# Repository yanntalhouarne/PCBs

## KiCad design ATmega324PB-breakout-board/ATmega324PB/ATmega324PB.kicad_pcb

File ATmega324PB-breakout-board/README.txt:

Breakout board for the ATmega324PB (automative rated)

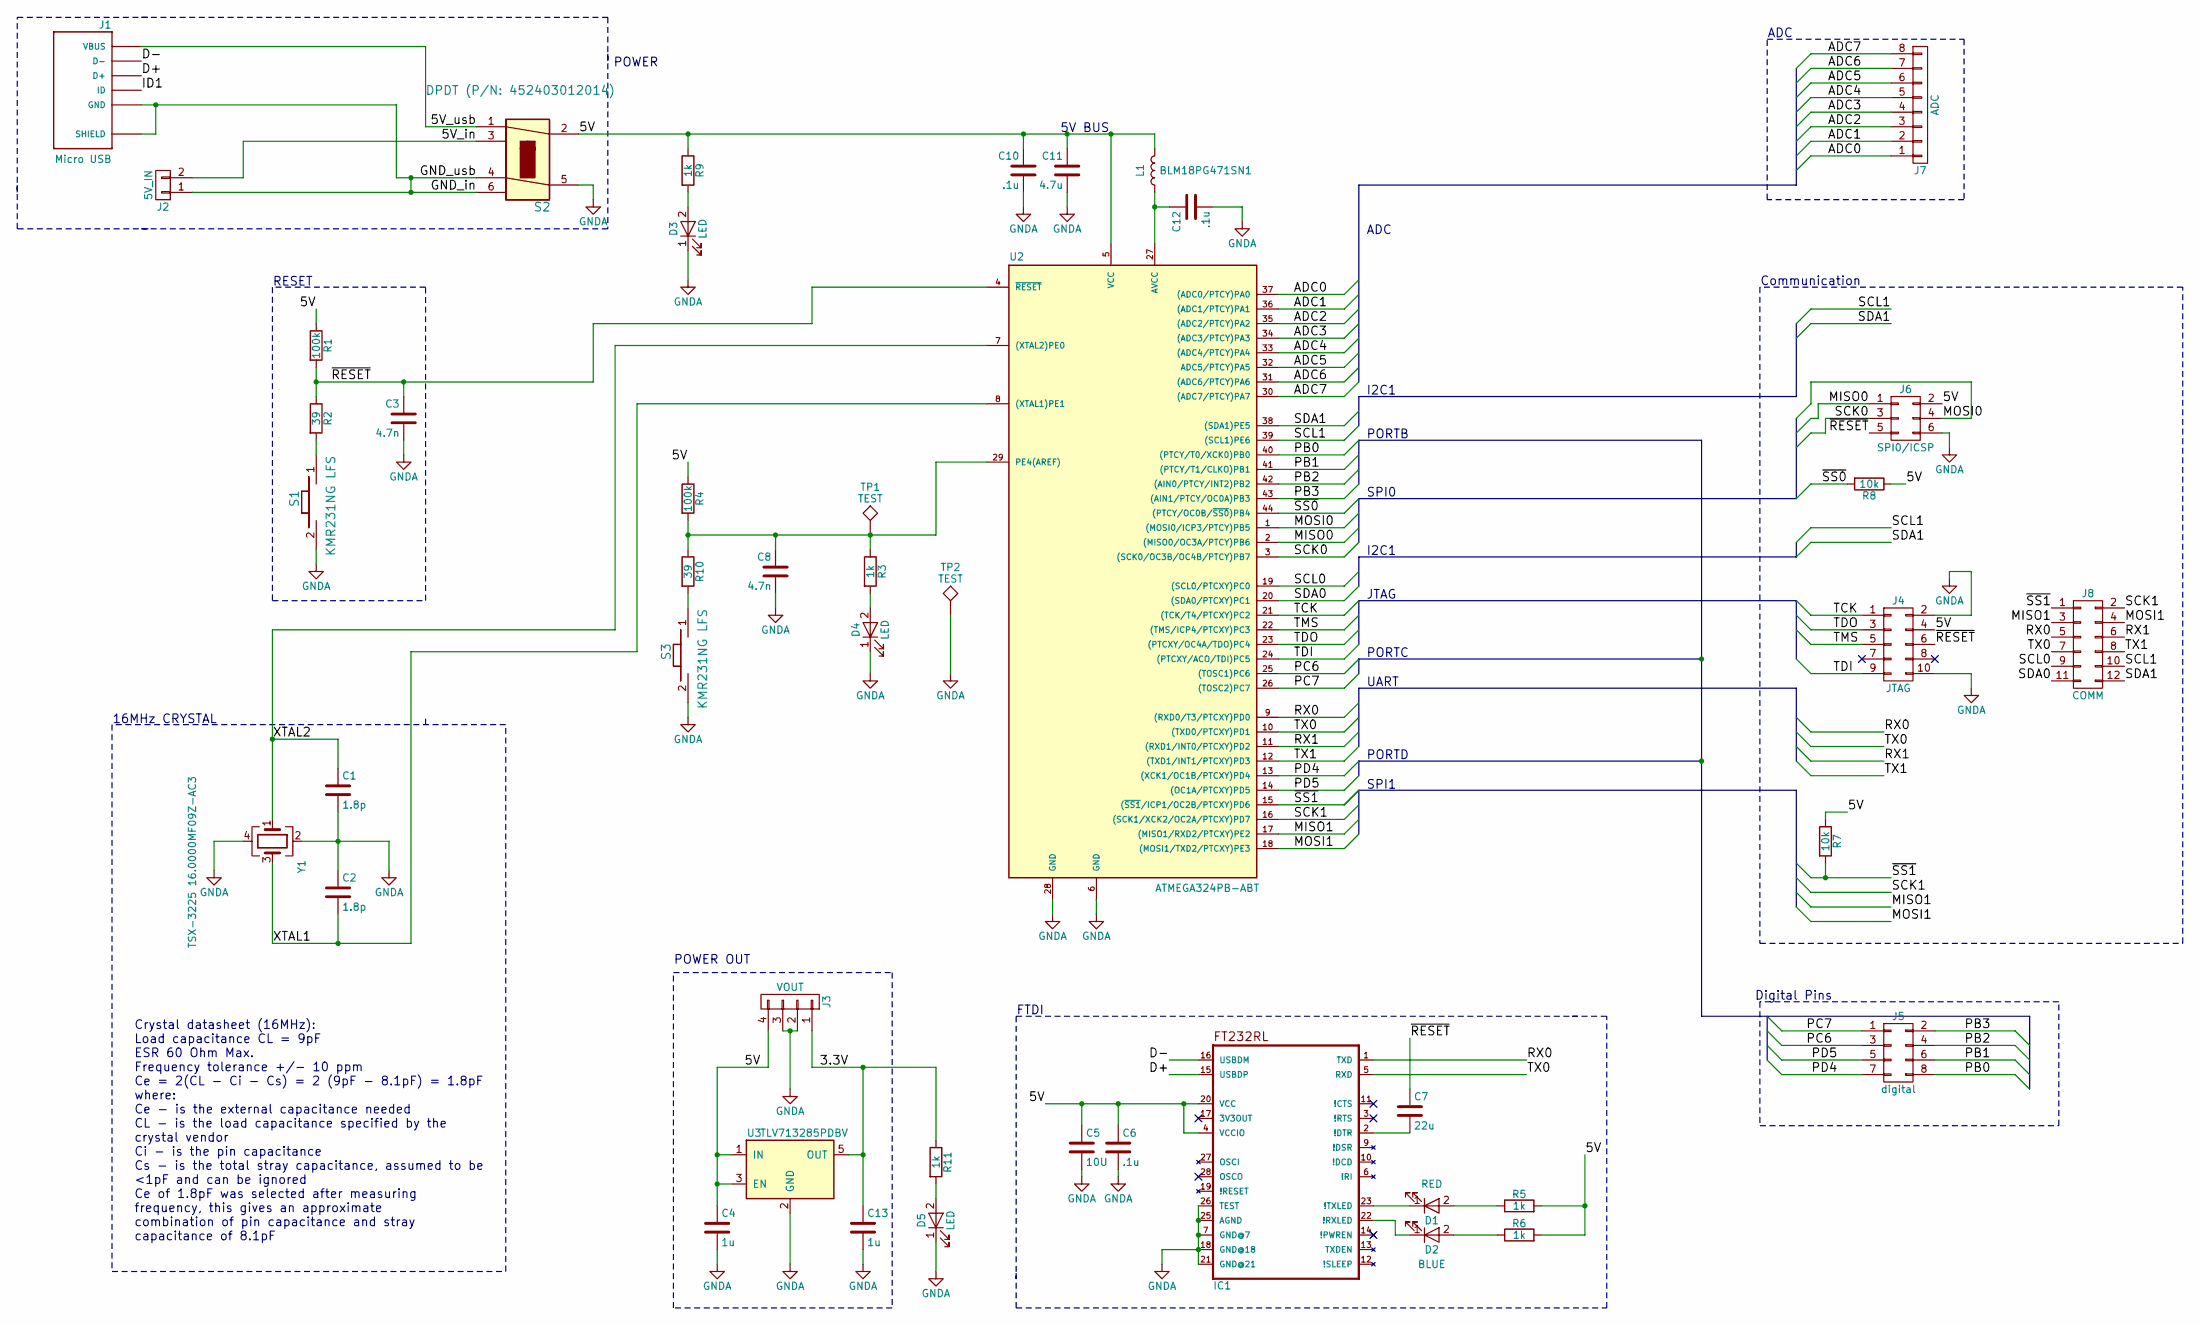
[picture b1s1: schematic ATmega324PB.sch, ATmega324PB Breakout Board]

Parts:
C1, C2: 1.8p; C_0402
C3, C8: 4.7n; C_0402
C4, C13: 1u; C_0402
C5: 10U; C_0603
C6, C10, C12: .1u; C_0402
C7: 22u; C_0603
C11: 4.7u; C_0603
D1: RED; LED_0603
D2: BLUE; LED_0603
D3, D4, D5: LED; LED_0603
IC1: FT232RL; SSOP28-LD
J1: Micro USB; USB_10118192-0001LF
J2: 5V_IN; Pin_Header_Straight_1x02_Pitch2.54mm
J3: VOUT; Pin_Header_Straight_1x04_Pitch2.54mm
J4: JTAG; Pin_Header_Straight_2x05_Pitch1.27mm
J5: digital; Pin_Header_Straight_2x04_Pitch2.54mm
J6: SPI0/ICSP; Pin_Header_Straight_2x03_Pitch2.54mm
J7: ADC; Pin_Header_Straight_1x08_Pitch2.54mm
J8: COMM; Pin_Header_Straight_2x06_Pitch2.54mm
L1: BLM18PG471SN1; L_0603
R1, R4: 100k; R_0402
R2, R10: 39; R_0402
R3: 1k; R_0603
R5, R6, R9, R11: 1k; R_0402
R7, R8: 10k; R_0402
S1, S3: KMR231NG LFS; SW_SPST_KMR2
S2: DPDT (P/N: 452403012014); JS202011SCQN
TP1, TP2: TEST; Pin_Header_Straight_1x01_Pitch1.00mm
U2: ATMEGA324PB-ABT; QFP80P1200X1200X120-44N
U3: TLV713285PDBV; SOT-23-5
Y1: TSX-3225 16.0000MF09Z-AC3; TSX_3225_16MF09ZAC3

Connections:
/3.3V: C13.1, J3.1, R11.1, U3.5 (OUT)
/5V: C4.1, C5.1, C6.1, C10.1, C11.1, IC1.4 (VCCIO), IC1.20 (VCC), J3.4, J4.4, J6.2, L1.2, R1.1, R4.1, R5.2, R6.2, R7.1, R8.1, R9.1, S2.2, U2.5 (VCC), U3.1 (IN), U3.3 (EN)
/5V_in: J2.2, S2.3
/5V_usb: J1.1 (VBUS), S2.1
/ADC0: J7.1, U2.37 ((ADC0/PTCY)PA0)
/ADC1: J7.2, U2.36 ((ADC1/PTCY)PA1)
/ADC2: J7.3, U2.35 ((ADC2/PTCY)PA2)
/ADC3: J7.4, U2.34 ((ADC3/PTCY)PA3)
/ADC4: J7.5, U2.33 ((ADC4/PTCY)PA4)
/ADC5: J7.6, U2.32 (ADC5/PTCY)PA5)
/ADC6: J7.7, U2.31 ((ADC6/PTCY)PA6)
/ADC7: J7.8, U2.30 ((ADC7/PTCY)PA7)
/D+: IC1.15 (USBDP), J1.3 (D+)
/D-: IC1.16 (USBDM), J1.2 (D-)
/GND_in: J1.5 (GND), J1.6 (SHIELD), J1.7 (SHIELD), J1.8 (SHIELD), J1.9 (SHIELD), J2.1, S2.4, S2.6
/MISO0: J6.1, U2.2 ((MISO0/OC3A/PTCY)PB6)
/MISO1: J8.3, U2.17 ((MISO1/RXD2/PTCXY)PE2)
/MOSI0: J6.4, U2.1 ((MOSI0/ICP3/PTCY)PB5)
/MOSI1: J8.4, U2.18 ((MOSI1/TXD2/PTCXY)PE3)
/PB0: J5.8, U2.40 ((PTCY/T0/XCK0)PB0)
/PB1: J5.6, U2.41 ((PTCY/T1/CLKO)PB1)
/PB2: J5.4, U2.42 ((AIN0/PTCY/INT2)PB2)
/PB3: J5.2, U2.43 ((AIN1/PTCY/OC0A)PB3)
/PC6: J5.3, U2.25 ((TOSC1)PC6)
/PC7: J5.1, U2.26 ((TOSC2)PC7)
/PD4: J5.7, U2.13 ((XCK1/OC1B/PTCXY)PD4)
/PD5: J5.5, U2.14 ((OC1A/PTCXY)PD5)
/RX0: IC1.1 (TXD), J8.5, U2.9 ((RXD0/T3/PTCXY)PD0)
/RX1: J8.6, U2.11 ((RXD1/INT0/PTCXY)PD2)
/SCK0: J6.3, U2.3 ((SCK0/OC3B/OC4B/PTCY)PB7)
/SCK1: J8.2, U2.16 ((SCK1/XCK2/OC2A/PTCXY)PD7)
/SCL0: J8.9, U2.19 ((SCL0/PTCXY)PC0)
/SCL1: J8.10, U2.39 ((SCL1)PE6)
/SDA0: J8.11, U2.20 ((SDA0/PTCXY)PC1)
/SDA1: J8.12, U2.38 ((SDA1)PE5)
/TCK: J4.1, U2.21 ((TCK/T4/PTCXY)PC2)
/TDI: J4.9, U2.24 ((PTCXY/ACO/TDI)PC5)
/TDO: J4.3, U2.23 ((PTCXY/OC4A/TDO)PC4)
/TMS: J4.5, U2.22 ((TMS/ICP4/PTCXY)PC3)
/TX0: IC1.5 (RXD), J8.7, U2.10 ((TXD0/PTCXY)PD1)
/TX1: J8.8, U2.12 ((TXD1/INT1/PTCXY)PD3)
/XTAL1: C2.2, U2.8 ((XTAL1)PE1), Y1.3
/XTAL2: C1.1, U2.7 ((XTAL2)PE0), Y1.1
/~RESET: C3.1, J4.6, J6.5, R1.2, R2.1, U2.4 (~RESET)
/~SS0~: R8.2, U2.44 ((PTCY/OC0B/~SS0~)PB4)
/~SS1~: J8.1, R7.2, U2.15 ((~SS1~/ICP1/OC2B/PTCXY)PD6)
GNDA: C1.2, C2.1, C3.2, C4.2, C5.2, C6.2, C8.2, C10.2, C11.2, C12.2, C13.2, D3.1 (K), D4.1 (K), D5.1 (K), IC1.7 (GND@7), IC1.18 (GND@18), IC1.21 (GND@21), IC1.25 (AGND), IC1.26 (TEST), J3.2, J3.3, J4.2, J4.10, J6.6, S1.2, S2.5, S3.2, TP2.1, U2.6 (GND), U2.28 (GND), U3.2 (GND), Y1.2, Y1.4
unnamed: C7.2, IC1.2 (!DTR)
unnamed: C8.1, R3.1, R4.2, R10.1, TP1.1, U2.29 (PE4(AREF))
unnamed: C12.1, L1.1, U2.27 (AVCC)
unnamed: D1.1 (K), IC1.23 (!TXLED)
unnamed: D1.2 (A), R5.1
unnamed: D2.1 (K), IC1.22 (!RXLED)
unnamed: D2.2 (A), R6.1
unnamed: D3.2 (A), R9.2
unnamed: D4.2 (A), R3.2
unnamed: D5.2 (A), R11.2
unnamed: R2.2, S1.1
unnamed: R10.2, S3.1

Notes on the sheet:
Crystal datasheet (16MHz): Load capacitance CL = 9pF ESR 60 Ohm Max. Frequency tolerance +/- 10 ppm Ce = 2(CL - Ci - Cs) = 2 (9pF - 8.1pF) = 1.8pF where: Ce - is the external capacitance needed CL - is the load capacitance specified by the crystal vendor Ci - is the pin capacitance Cs - is the tota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
RESET
16MHz CRYSTAL
SPI0
SPI1
POWER
ADC
5V BUS
I2C1
I2C1
UART
PORTB
PORTC
Communication
ADC
Digital Pins
JTAG
PORTD
FTDI
POWER OUT

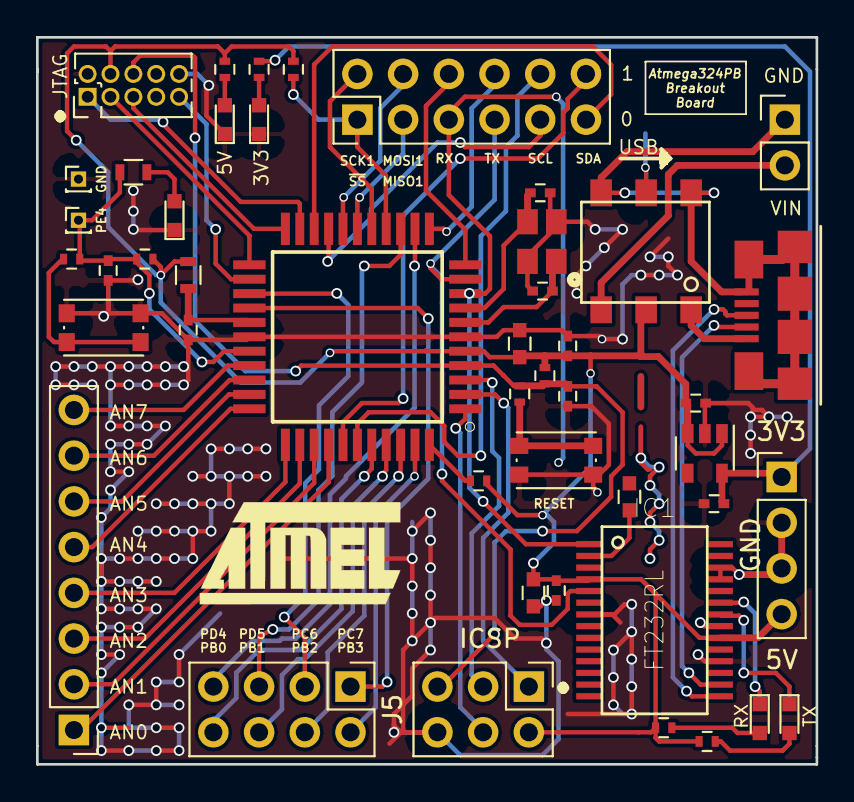
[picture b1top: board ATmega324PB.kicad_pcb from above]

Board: 2 copper layers, 43.3 x 40.4 mm, 46 parts (0 on the bottom side), 59 nets.

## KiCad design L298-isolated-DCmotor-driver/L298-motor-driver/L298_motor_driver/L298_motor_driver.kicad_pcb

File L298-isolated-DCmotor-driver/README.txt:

A motor driver board bsed on the LN298 H-bridge chip. It can take a li-po battery as input with a xt-60 connector or it can be powered with a power supply. Input volatage ratings are printed on the back side of the board. The control inputs are optically isolated. The board offers a 5V isolated output to power the controller board.

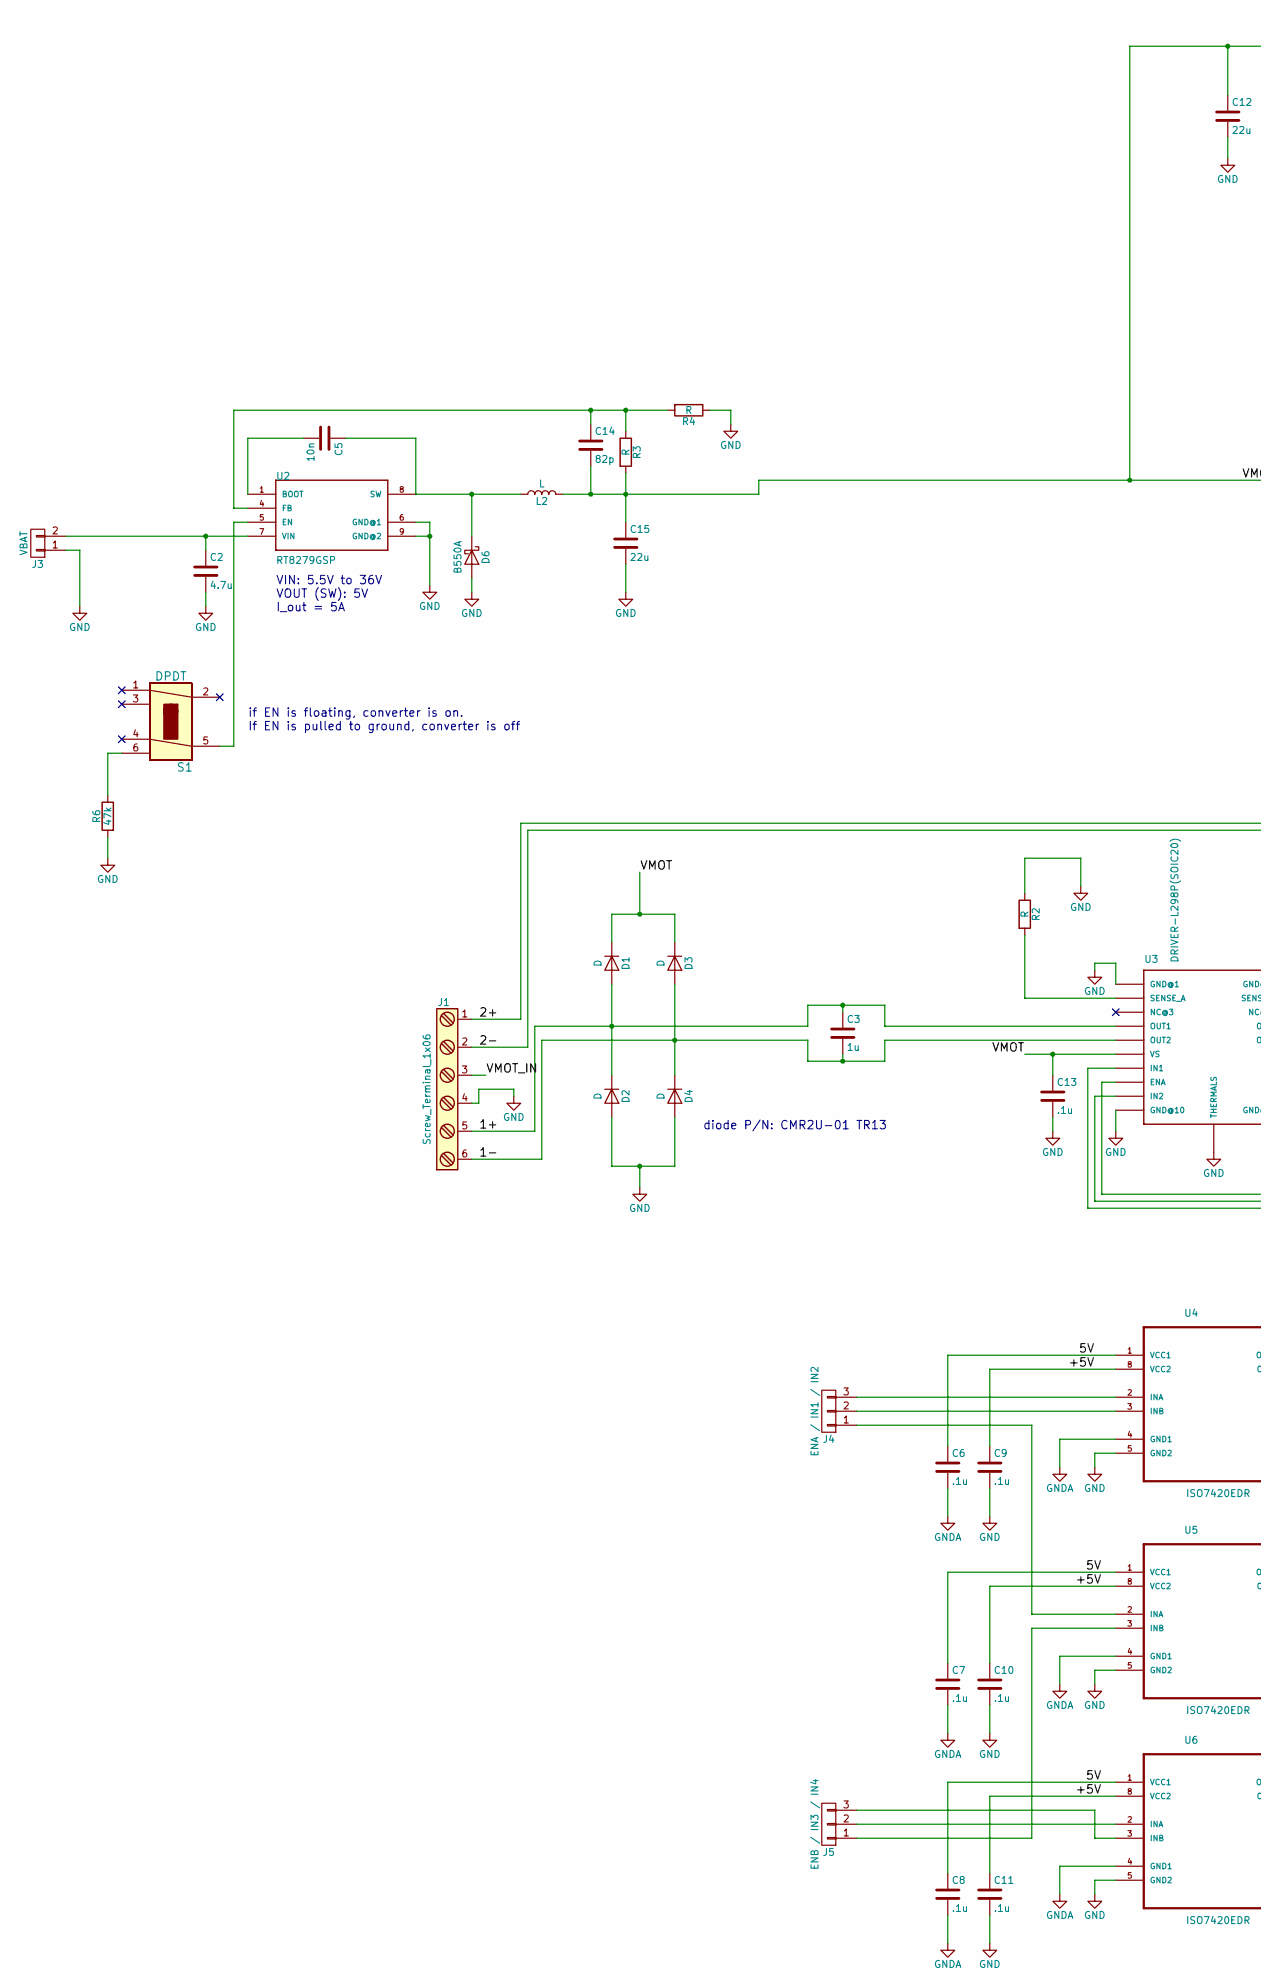
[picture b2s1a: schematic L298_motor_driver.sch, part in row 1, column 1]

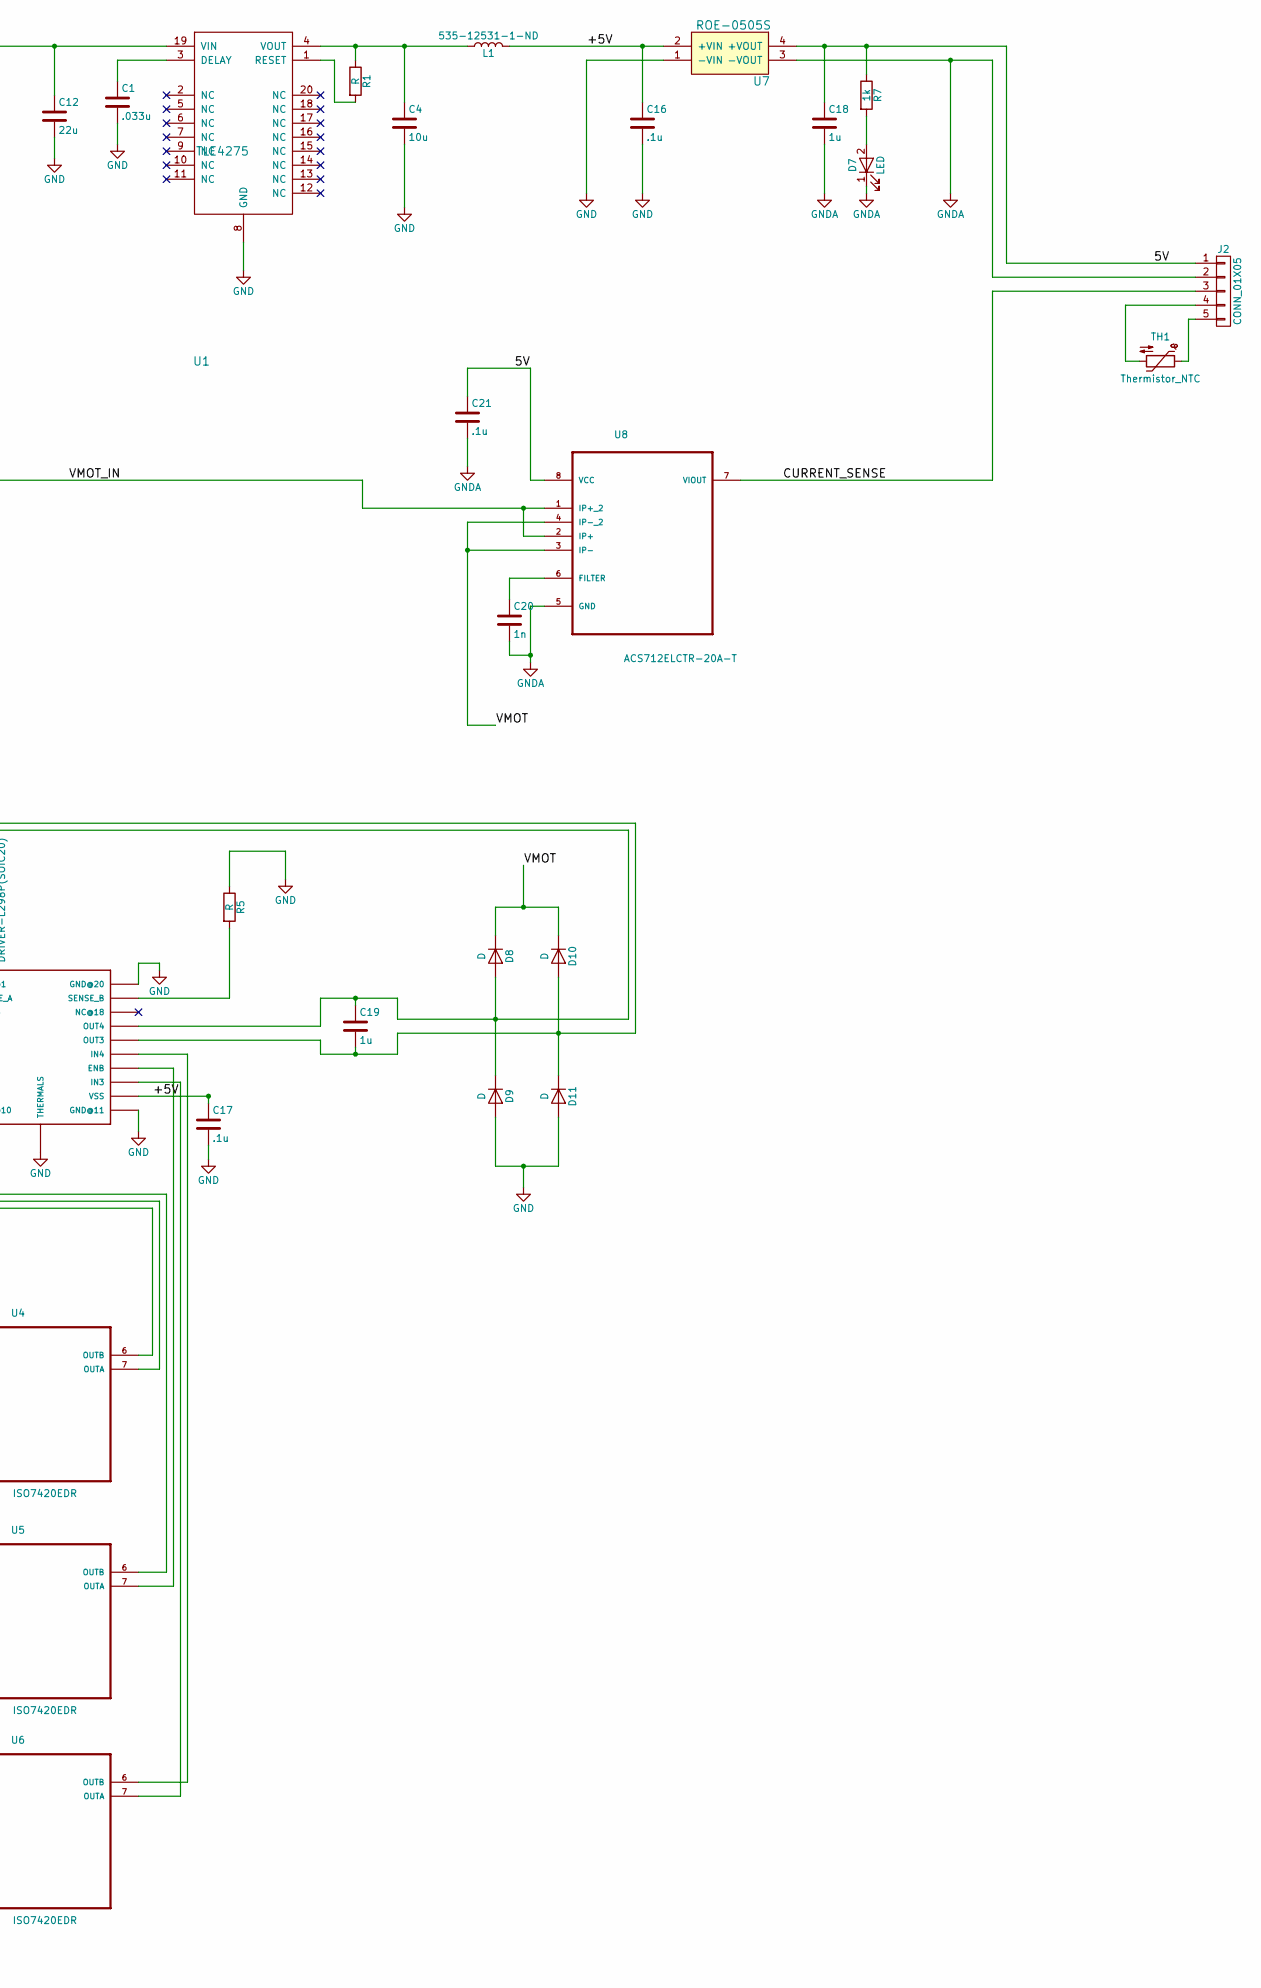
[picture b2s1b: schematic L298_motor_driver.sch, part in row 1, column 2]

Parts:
C1: .033u; C_0603
C2: 4.7u; C_0603
C3, C18, C19: 1u; C_0603
C4: 10u; C_0805
C5: 10n; C_0603
C6, C7, C8, C9, C10, C11, C13, C17: .1u; C_0402
C12, C15: 22u; C_0603
C14: 82p; C_0603
C16, C21: .1u; C_0603
C20: 1n; C_0603
D1, D2, D3, D4, D8, D9, D10, D11: D; D_SMB_Handsoldering
D6: B550A; D_SMB_Handsoldering
D7: LED; LED_0603
J1: Screw_Terminal_1x06; Pin_Header_Straight_1x06_Pitch2.54mm
J2: CONN_01X05; Pin_Header_Straight_1x05_Pitch2.54mm
J3: VBAT; XT60
J4: ENA / IN1 / IN2; Pin_Header_Straight_1x03_Pitch2.54mm
J5: ENB / IN3 / IN4; Pin_Header_Straight_1x03_Pitch2.54mm
L1: 535-12531-1-ND; L_0603_HandSoldering
L2: L; INDUCTOR_744770115
R1, R2, R3, R4, R5: R; R_0402
R6: 47k; R_0402
R7: 1k; R_0402
S1: DPDT; JS202011SCQN
TH1: Thermistor_NTC; R_0402
U1: TLE4275; TSSOP-20_4.4x6.5mm_Pitch0.65mm
U2: RT8279GSP; SOIC127P600X175-9N
U3: DRIVER-L298P(SOIC20); SOIC20G-1.27-16X11MM
U4, U5, U6: ISO7420EDR; SOIC-8_3.9x4.9mm_Pitch1.27mm
U7: ROE-0505S; Pin_Header_Straight_1x04_Pitch2.54mm
U8: ACS712ELCTR-20A-T; SOIC-8_3.9x4.9mm_Pitch1.27mm

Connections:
/1+: C3.1, D1.2 (A), D2.1 (K), J1.5, U3.P$4 (OUT1)
/1-: C3.2, D3.2 (A), D4.1 (K), J1.6, U3.P$5 (OUT2)
/2+: C19.2, D10.2 (A), D11.1 (K), J1.1, U3.P$16 (OUT3)
/2-: C19.1, D8.2 (A), D9.1 (K), J1.2, U3.P$17 (OUT4)
/5V: C6.1, C7.1, C8.1, C18.1, C21.1, J2.1, R7.1, U4.1 (VCC1), U5.1 (VCC1), U6.1 (VCC1), U7.4 (+VOUT), U8.8 (VCC)
/+5V: C9.1, C10.1, C11.1, C16.1, C17.1, L1.2, U3.P$12 (VSS), U4.8 (VCC2), U5.8 (VCC2), U6.8 (VCC2), U7.2 (+VIN)
/CURRENT_SENSE: J2.3, U8.7 (VIOUT)
/VMOT: C13.1, D1.1 (K), D3.1 (K), D8.1 (K), D10.1 (K), U3.P$6 (VS), U8.3 (IP-), U8.4 (IP-_2)
/VMOT_IN: C12.1, C14.2, C15.1, J1.3, L2.2, R3.2, U1.19 (VIN), U8.1 (IP+_2), U8.2 (IP+)
GND: C1.2, C2.2, C4.2, C9.2, C10.2, C11.2, C12.2, C13.2, C15.2, C16.2, C17.2, D2.2 (A), D4.2 (A), D6.2 (A), D9.2 (A), D11.2 (A), J1.4, J3.1, R2.1, R4.1, R5.1, R6.2, U1.8 (GND), U2.6 (GND@1), U2.9 (GND@2), U3.P$1 (GND@1), U3.P$10 (GND@10), U3.P$11 (GND@11), U3.P$20 (GND@20), U3.THER (THERMALS), U4.5 (GND2), U5.5 (GND2), U6.5 (GND2), U7.1 (-VIN)
GNDA: C6.2, C7.2, C8.2, C18.2, C20.2, C21.2, D7.1 (K), J2.2, U4.4 (GND1), U5.4 (GND1), U6.4 (GND1), U7.3 (-VOUT), U8.5 (GND)
unnamed: C1.1, U1.3 (DELAY)
unnamed: C2.1, J3.2, U2.7 (VIN)
unnamed: C4.1, L1.1, R1.1, U1.4 (VOUT)
unnamed: C5.1, D6.1 (K), L2.1, U2.8 (SW)
unnamed: C5.2, U2.1 (BOOT)
unnamed: C14.1, R3.1, R4.2, U2.4 (FB)
unnamed: C20.1, U8.6 (FILTER)
unnamed: D7.2 (A), R7.2
unnamed: J2.4, TH1.2
unnamed: J2.5, TH1.1
unnamed: J4.1, U5.2 (INA)
unnamed: J4.2, U4.3 (INB)
unnamed: J4.3, U4.2 (INA)
unnamed: J5.1, U5.3 (INB)
unnamed: J5.2, U6.2 (INA)
unnamed: J5.3, U6.3 (INB)
unnamed: R1.2, U1.1 (RESET)
unnamed: R2.2, U3.P$2 (SENSE_A)
unnamed: R5.2, U3.P$19 (SENSE_B)
unnamed: R6.1, S1.6
unnamed: S1.5, U2.5 (EN)
unnamed: U3.P$7 (IN1), U4.6 (OUTB)
unnamed: U3.P$8 (ENA), U5.6 (OUTB)
unnamed: U3.P$9 (IN2), U4.7 (OUTA)
unnamed: U3.P$13 (IN3), U6.7 (OUTA)
unnamed: U3.P$14 (ENB), U5.7 (OUTA)
unnamed: U3.P$15 (IN4), U6.6 (OUTB)

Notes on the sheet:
VIN: 5.5V to 36V VOUT (SW): 5V I_out = 5A
if EN is floating, converter is on. If EN is pulled to ground, converter is off
diode P/N: CMR2U-01 TR13

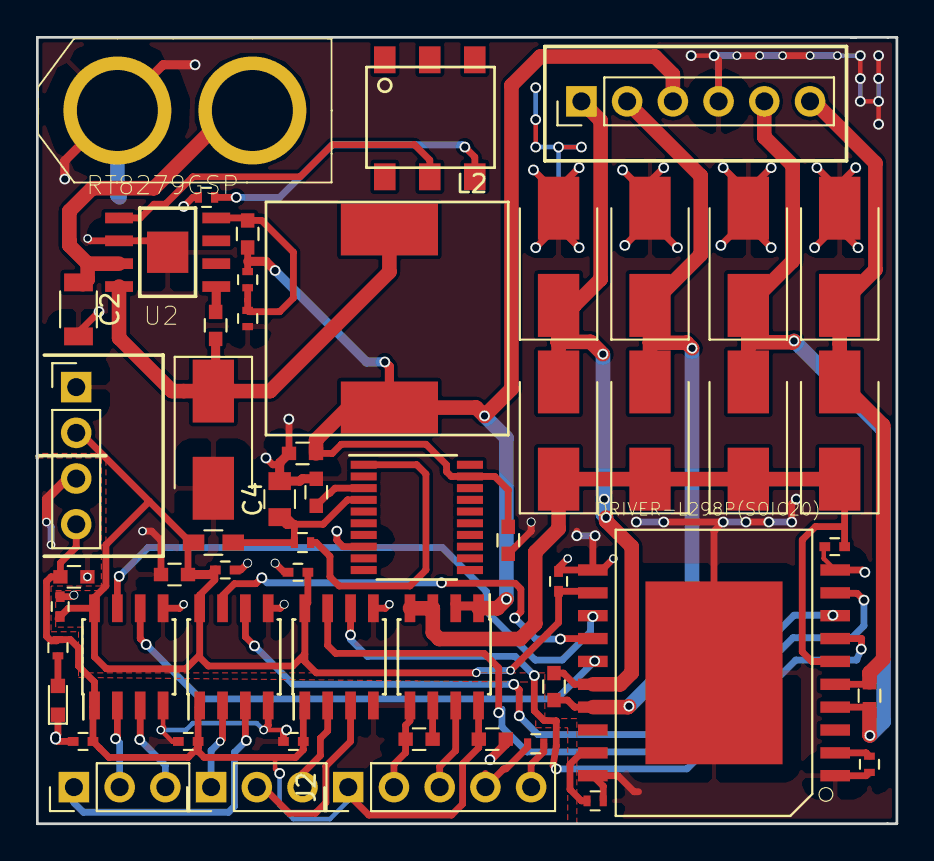
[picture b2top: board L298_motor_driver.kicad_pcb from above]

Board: 2 copper layers, 47.8 x 43.7 mm, 55 parts (0 on the bottom side), 38 nets.

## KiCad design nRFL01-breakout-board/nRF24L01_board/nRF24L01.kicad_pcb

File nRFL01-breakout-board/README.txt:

Breakout board for the nRF24L01 with SMA output for antenna.

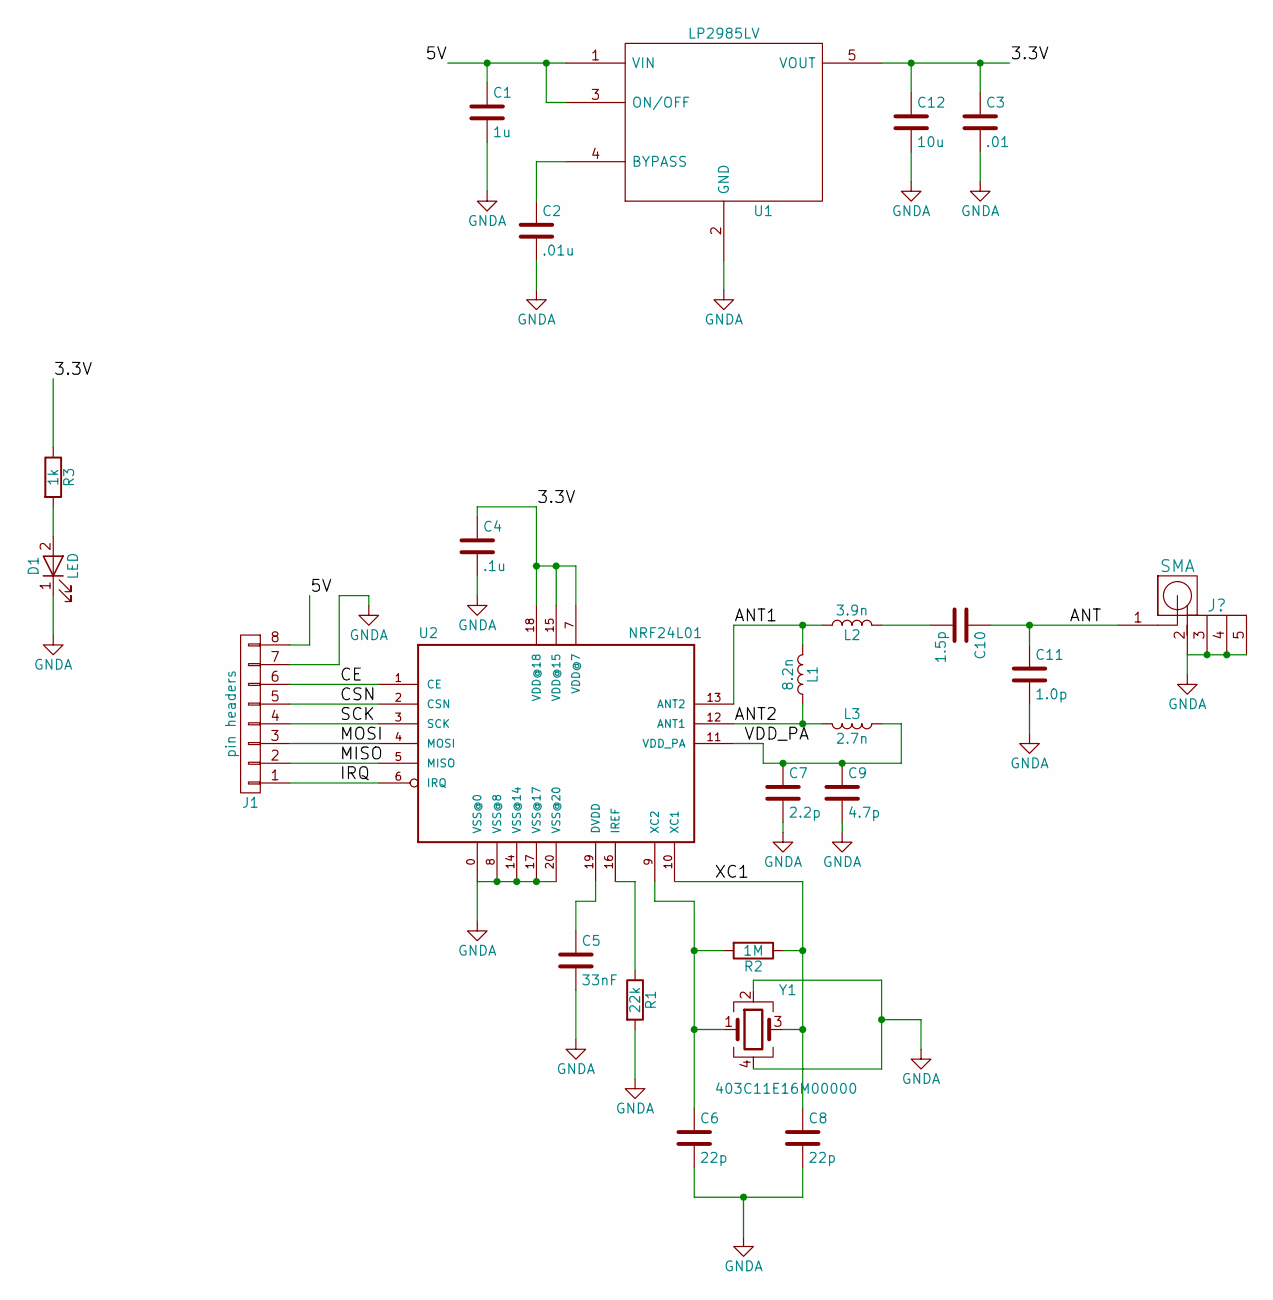
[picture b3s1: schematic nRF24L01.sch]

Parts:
C1: 1u; C_0402
C2: .01u; C_0402
C3: .01; C_0402
C4: .1u; C_0402
C5: 33nF; C_0402
C6, C8: 22p; C_0402
C7: 2.2p; C_0402
C9: 4.7p; C_0402
C10: 1.5p; C_0402
C11: 1.0p; C_0402
C12: 10u; C_0603
D1: LED; LED_0603
J1: pin headers; Pin_Header_Straight_1x08_Pitch2.54mm
L1: 8.2n; L_0402
L2: 3.9n; L_0402
L3: 2.7n; L_0402
R1: 22k; L_0402
R2: 1M; L_0402
R3: 1k; R_0402
U1: LP2985LV; SOT95P280X145-5N
U2: NRF24L01; QFN20
Y1: 403C11E16M00000

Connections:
/3.3V: C3.1, C4.1, C12.1, R3.1, U1.5 (VOUT), U2.7 (VDD@7), U2.15 (VDD@15), U2.18 (VDD@18)
/5V: C1.1, J1.8, U1.1 (VIN), U1.3 (ON/OFF)
/ANT: C10.1, C11.1; also elsewhere on the board
/ANT1: L1.2, L2.1, U2.13 (ANT2)
/ANT2: L1.1, L3.2, U2.12 (ANT1)
/CE: J1.6, U2.1 (CE)
/CSN: J1.5, U2.2 (CSN)
/IRQ: J1.1, U2.6 (IRQ)
/MISO: J1.2, U2.5 (MISO)
/MOSI: J1.3, U2.4 (MOSI)
/SCK: J1.4, U2.3 (SCK)
/VDD_PA: C7.1, C9.1, L3.1, U2.11 (VDD_PA)
/XC1: C8.1, R2.1, U2.10 (XC1), Y1.3
GNDA: C1.2, C2.2, C3.2, C4.2, C5.2, C6.2, C7.2, C8.2, C9.2, C11.2, C12.2, D1.1 (K), J1.7, R1.2, U1.2 (GND), U2.0 (VSS@0), U2.8 (VSS@8), U2.14 (VSS@14), U2.17 (VSS@17), U2.20 (VSS@20), Y1.2, Y1.4; also elsewhere on the board
unnamed: C2.1, U1.4 (BYPASS)
unnamed: C5.1, U2.19 (DVDD)
unnamed: C6.1, R2.2, U2.9 (XC2), Y1.1
unnamed: C10.2, L2.2
unnamed: D1.2 (A), R3.2
unnamed: R1.1, U2.16 (IREF)

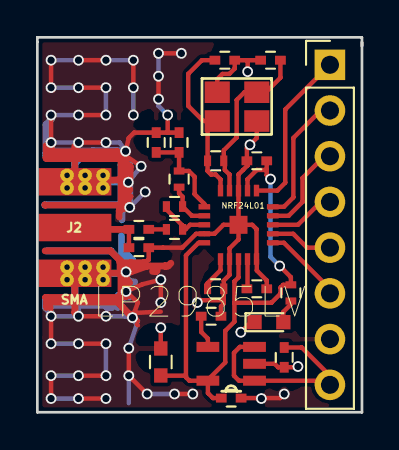
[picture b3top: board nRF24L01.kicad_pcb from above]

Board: 2 copper layers, 18.0 x 20.8 mm, 24 parts (0 on the bottom side), 20 nets.

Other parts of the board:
J2: SMA; SMA-EDGE

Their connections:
/ANT: J2.1; also elsewhere on the board
GNDA: J2.2, J2.3, J2.4, J2.5; also elsewhere on the board

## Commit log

2018-02-18 Added first boards.
